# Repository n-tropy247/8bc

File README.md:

# 8bc
8-bit computer on PCB using [Ben Eater's architecture](https://eater.net/8bit)

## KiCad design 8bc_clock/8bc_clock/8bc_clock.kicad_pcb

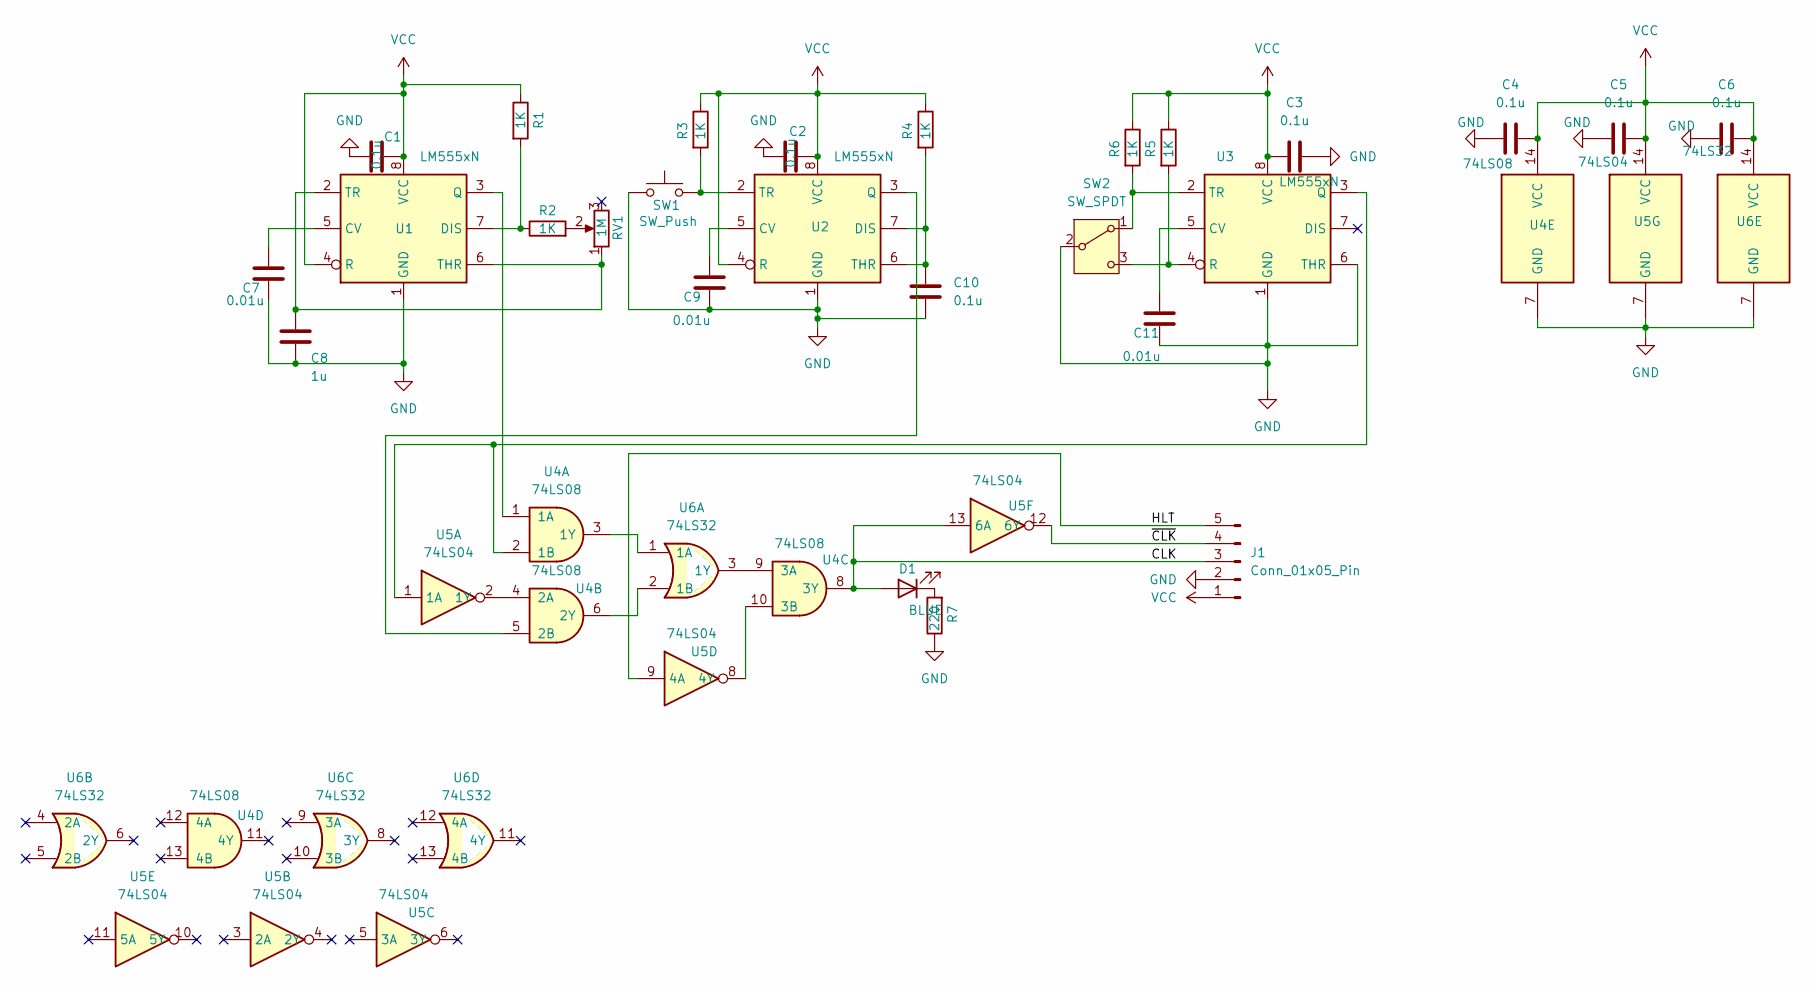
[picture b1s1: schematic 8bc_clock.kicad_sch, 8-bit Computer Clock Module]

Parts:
C1, C2, C3, C4, C5, C6, C10: 0.1u; C_Disc_D3.0mm_W1.6mm_P2.50mm
C7, C9, C11: 0.01u; C_Disc_D3.0mm_W1.6mm_P2.50mm
C8: 1u; C_Disc_D3.0mm_W1.6mm_P2.50mm
D1: BLUE; LED_D3.0mm
J1: Conn_01x05_Pin; PinHeader_1x05_P2.00mm_Vertical
R1, R2, R3, R4, R5, R6: 1K; R_Axial_DIN0204_L3.6mm_D1.6mm_P2.54mm_Vertical
R7: 220; R_Axial_DIN0204_L3.6mm_D1.6mm_P2.54mm_Vertical
RV1: 1M; Potentiometer_Alpha_RD901F-40-00D_Single_Vertical
SW1: SW_Push; SW_PUSH_1P1T_6x3.5mm_H5.0_APEM_MJTP1250
SW2: SW_SPDT; SW_Slide-03_Wuerth-WS-SLTV_10x2.5x6.4_P2.54mm
U1, U2, U3: LM555xN; DIP-8_W7.62mm
U4: 74LS08; DIP-14_W7.62mm_Socket
U5: 74LS04; DIP-14_W7.62mm_Socket
U6: 74LS32; DIP-14_W7.62mm_Socket

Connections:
/CLK: D1.2 (A), J1.3, U4.8 (3Y), U5.13 (6A)
/HLT: J1.5, U5.9 (4A)
/~CLK: J1.4, U5.12 (6Y)
GND: C1.1, C2.1, C3.1, C4.1, C5.1, C6.1, C7.2, C8.2, C9.2, C10.2, C11.2, J1.2, R7.1, SW1.1, SW2.2 (B), U1.1 (GND), U2.1 (GND), U3.1 (GND), U3.6 (THR), U4.7 (GND), U5.7 (GND), U6.7 (GND)
unnamed: D1.1 (K), R7.2
unnamed: R2.2, RV1.2
unnamed: R6.2, SW2.1 (A), U3.2 (TR)
unnamed: R5.2, SW2.3 (C), U3.4 (R)
unnamed: C7.1, U1.5 (CV)
unnamed: R1.2, R2.1, U1.7 (DIS)
unnamed: U1.3 (Q), U4.1 (1A)
unnamed: C8.1, RV1.1, U1.2 (TR), U1.6 (THR)
unnamed: C9.1, U2.5 (CV)
unnamed: C10.1, R4.2, U2.6 (THR), U2.7 (DIS)
unnamed: U2.3 (Q), U4.5 (2B)
unnamed: R3.2, SW1.2, U2.2 (TR)
unnamed: C11.1, U3.5 (CV)
unnamed: U3.3 (Q), U4.2 (1B), U5.1 (1A)
unnamed: U4.3 (1Y), U6.1 (1A)
unnamed: U4.4 (2A), U5.2 (1Y)
unnamed: U4.6 (2Y), U6.2 (1B)
unnamed: U4.9 (3A), U6.3 (1Y)
unnamed: U4.10 (3B), U5.8 (4Y)
VCC: C1.2, C2.2, C3.2, C4.2, C5.2, C6.2, J1.1, R1.1, R3.1, R4.1, R5.1, R6.1, U1.4 (R), U1.8 (VCC), U2.4 (R), U2.8 (VCC), U3.8 (VCC), U4.14 (VCC), U5.14 (VCC), U6.14 (VCC)

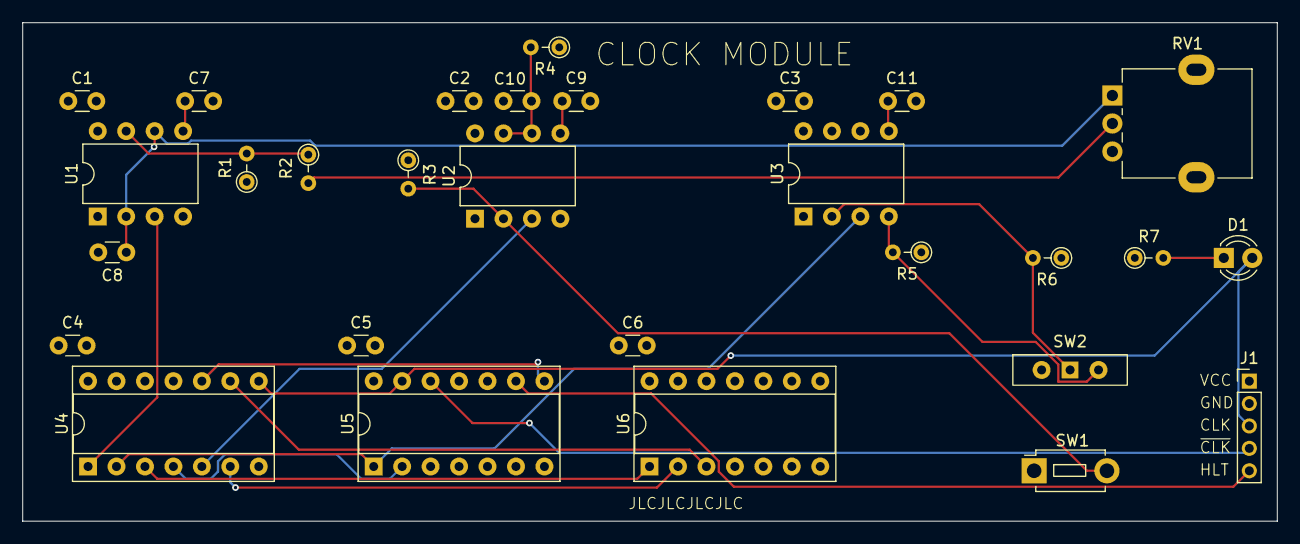
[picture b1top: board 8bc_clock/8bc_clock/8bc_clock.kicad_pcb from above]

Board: 4 copper layers, 112.0 x 44.5 mm, 29 parts (0 on the bottom side), 24 nets.

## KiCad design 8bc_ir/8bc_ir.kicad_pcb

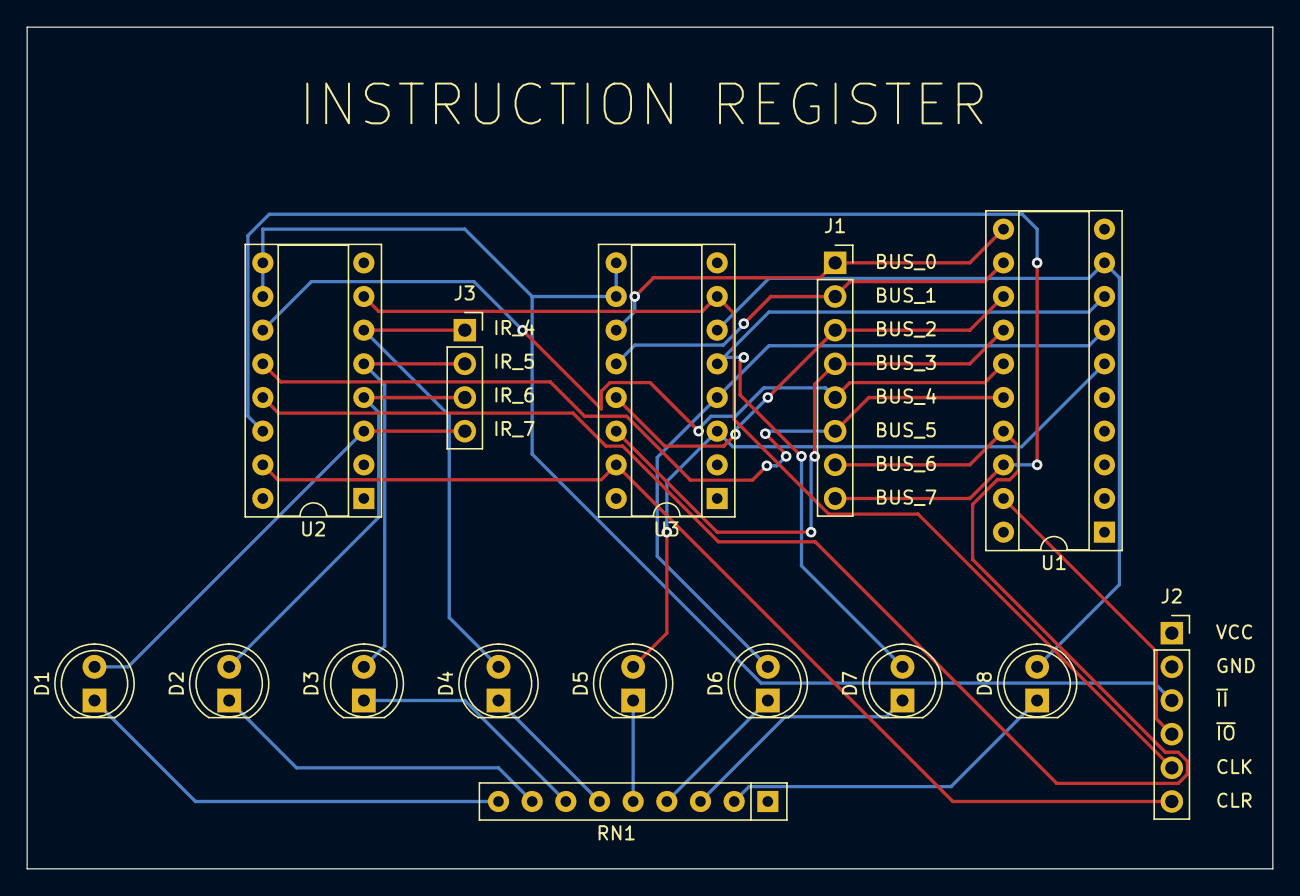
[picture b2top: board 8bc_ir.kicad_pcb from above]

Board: 4 copper layers, 94.0 x 63.5 mm, 15 parts (0 on the bottom side), 30 nets.

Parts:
D1, D2, D3, D4: BLUE; LED_D5.0mm
D5, D6, D7, D8: YELLOW; LED_D5.0mm
J1: Conn_01x08_Pin; PinSocket_1x08_P2.54mm_Vertical
J2: Conn_01x06_Pin; PinSocket_1x06_P2.54mm_Vertical
J3: Conn_01x04_Pin; PinSocket_1x04_P2.54mm_Vertical
RN1: 220; R_Array_SIP9
U1: 74LS245; DIP-20_W7.62mm_Socket
U2, U3: 74LS173; DIP-16_W7.62mm_Socket

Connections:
/BUS_0: J1.1, U1.11 (B7), U3.11 (D3)
/BUS_1: J1.2, U1.12 (B6), U3.12 (D2)
/BUS_2: J1.3, U1.13 (B5), U3.13 (D1)
/BUS_3: J1.4, U1.14 (B4), U3.14 (D0)
/BUS_4: J1.5, U1.15 (B3), U2.11 (D3)
/BUS_5: J1.6, U1.16 (B2), U2.12 (D2)
/BUS_6: J1.7, U1.17 (B1), U2.13 (D1)
/BUS_7: J1.8, U1.18 (B0), U2.14 (D0)
/CLK: J2.5, U2.7 (Cp), U3.7 (Cp)
/CLR: J2.6, U2.15 (Mr), U3.15 (Mr)
/GND: J2.2, RN1.1 (common), U1.10 (GND), U2.1 (Oe1), U2.2 (Oe2), U2.8 (GND), U3.1 (Oe1), U3.2 (Oe2), U3.8 (GND)
/IR_4: D4.2 (A), J3.1, U2.6 (Q3)
/IR_5: D3.2 (A), J3.2, U2.5 (Q2)
/IR_6: D2.2 (A), J3.3, U2.4 (Q1)
/IR_7: D1.2 (A), J3.4, U2.3 (Q0)
/VCC: J2.1, U1.1 (A->B), U1.20 (VCC), U2.16 (VCC), U3.16 (VCC)
/~II: J2.3, U2.9 (E1), U2.10 (E2), U3.9 (E1), U3.10 (E2)
/~IO: J2.4, U1.19 (CE)
unnamed: D1.1 (K), RN1.9 (R8)
unnamed: D2.1 (K), RN1.8 (R7)
unnamed: D3.1 (K), RN1.7 (R6)
unnamed: D4.1 (K), RN1.6 (R5)
unnamed: D5.2 (A), U1.6 (A4), U3.3 (Q0)
unnamed: D5.1 (K), RN1.5 (R4)
unnamed: D6.2 (A), U1.7 (A5), U3.4 (Q1)
unnamed: D6.1 (K), RN1.4 (R3)
unnamed: D7.2 (A), U1.8 (A6), U3.5 (Q2)
unnamed: D7.1 (K), RN1.3 (R2)
unnamed: D8.2 (A), U1.9 (A7), U3.6 (Q3)
unnamed: D8.1 (K), RN1.2 (R1)

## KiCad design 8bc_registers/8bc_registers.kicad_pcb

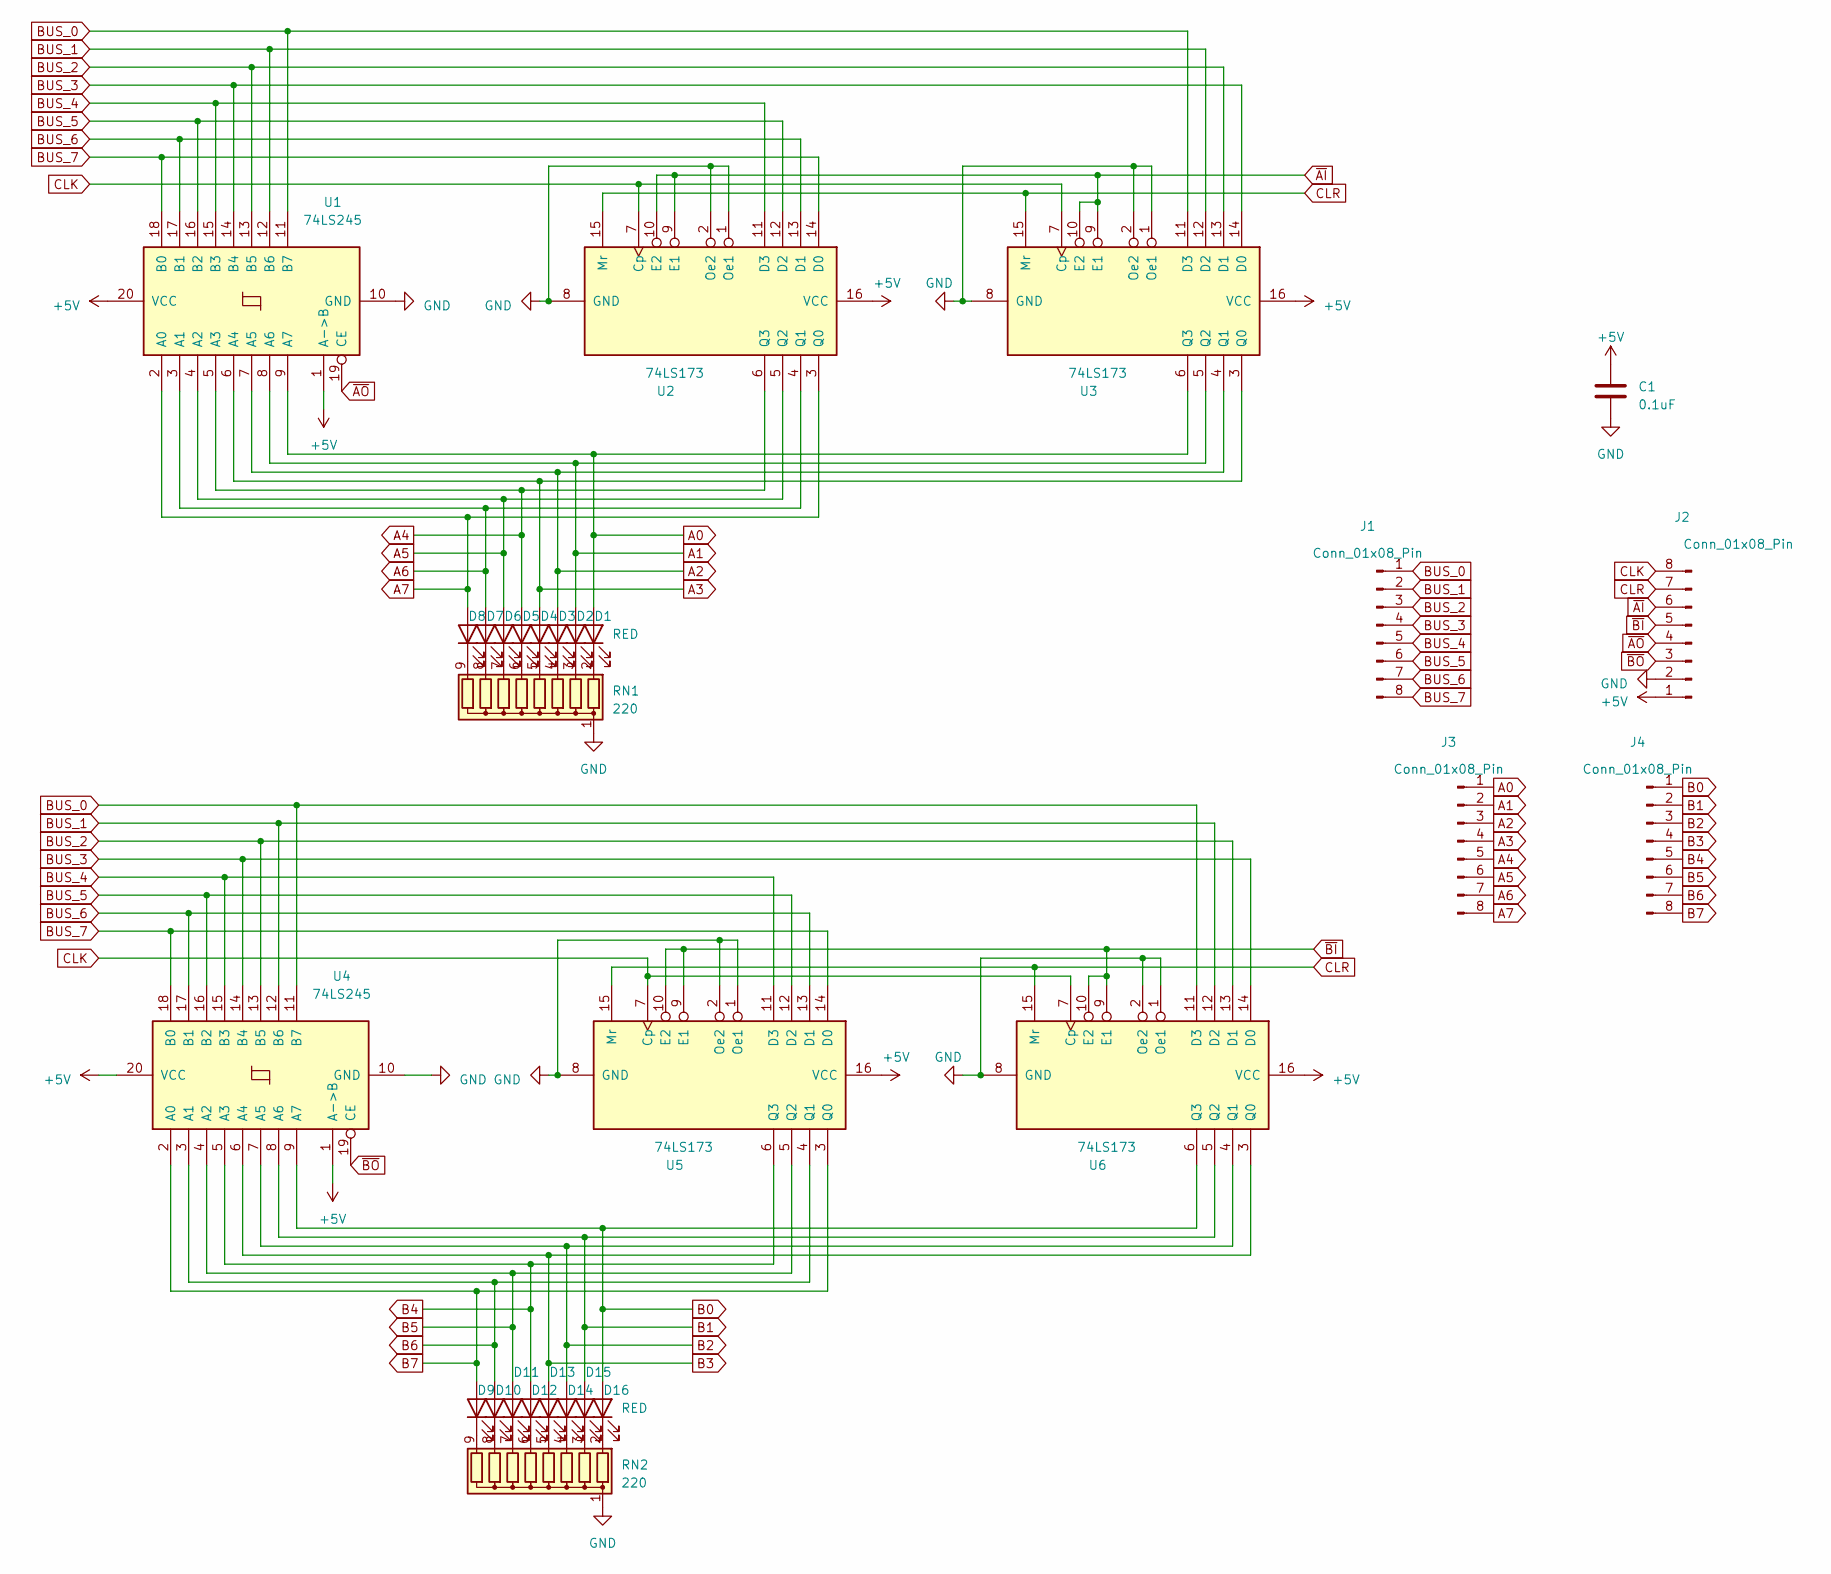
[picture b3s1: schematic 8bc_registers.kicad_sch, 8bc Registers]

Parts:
C1: 0.1uF; CP_Radial_Tantal_D5.0mm_P2.50mm
D1, D2, D3, D4, D5, D6, D7, D8, D9, D10, D11, D12, D13, D14, D15, D16: RED; LED_D8.0mm
J1, J2, J3, J4: Conn_01x08_Pin; PinSocket_1x08_P2.54mm_Vertical
RN1, RN2: 220; R_Array_SIP9
U1, U4: 74LS245; DIP-20_W7.62mm_Socket
U2, U3, U5, U6: 74LS173; DIP-16_W7.62mm_Socket

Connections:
+5V: C1.1, J2.1, U1.1 (A->B), U1.20 (VCC), U2.16 (VCC), U3.16 (VCC), U4.1 (A->B), U4.20 (VCC), U5.16 (VCC), U6.16 (VCC)
A0: D1.2 (A), J3.1, U1.9 (A7), U3.6 (Q3)
A1: D2.2 (A), J3.2, U1.8 (A6), U3.5 (Q2)
A2: D3.2 (A), J3.3, U1.7 (A5), U3.4 (Q1)
A3: D4.2 (A), J3.4, U1.6 (A4), U3.3 (Q0)
A4: D5.2 (A), J3.5, U1.5 (A3), U2.6 (Q3)
A5: D6.2 (A), J3.6, U1.4 (A2), U2.5 (Q2)
A6: D7.2 (A), J3.7, U1.3 (A1), U2.4 (Q1)
A7: D8.2 (A), J3.8, U1.2 (A0), U2.3 (Q0)
B0: D16.2 (A), J4.1, U4.9 (A7), U6.6 (Q3)
B1: D15.2 (A), J4.2, U4.8 (A6), U6.5 (Q2)
B2: D14.2 (A), J4.3, U4.7 (A5), U6.4 (Q1)
B3: D13.2 (A), J4.4, U4.6 (A4), U6.3 (Q0)
B4: D12.2 (A), J4.5, U4.5 (A3), U5.6 (Q3)
B5: D11.2 (A), J4.6, U4.4 (A2), U5.5 (Q2)
B6: D10.2 (A), J4.7, U4.3 (A1), U5.4 (Q1)
B7: D9.2 (A), J4.8, U4.2 (A0), U5.3 (Q0)
BUS_0: J1.1, U1.11 (B7), U3.11 (D3), U4.11 (B7), U6.11 (D3)
BUS_1: J1.2, U1.12 (B6), U3.12 (D2), U4.12 (B6), U6.12 (D2)
BUS_2: J1.3, U1.13 (B5), U3.13 (D1), U4.13 (B5), U6.13 (D1)
BUS_3: J1.4, U1.14 (B4), U3.14 (D0), U4.14 (B4), U6.14 (D0)
BUS_4: J1.5, U1.15 (B3), U2.11 (D3), U4.15 (B3), U5.11 (D3)
BUS_5: J1.6, U1.16 (B2), U2.12 (D2), U4.16 (B2), U5.12 (D2)
BUS_6: J1.7, U1.17 (B1), U2.13 (D1), U4.17 (B1), U5.13 (D1)
BUS_7: J1.8, U1.18 (B0), U2.14 (D0), U4.18 (B0), U5.14 (D0)
CLK: J2.8, U2.7 (Cp), U3.7 (Cp), U5.7 (Cp), U6.7 (Cp)
CLR: J2.7, U2.15 (Mr), U3.15 (Mr), U5.15 (Mr), U6.15 (Mr)
GND: C1.2, J2.2, RN1.1 (common), RN2.1 (common), U1.10 (GND), U2.1 (Oe1), U2.2 (Oe2), U2.8 (GND), U3.1 (Oe1), U3.2 (Oe2), U3.8 (GND), U4.10 (GND), U5.1 (Oe1), U5.2 (Oe2), U5.8 (GND), U6.1 (Oe1), U6.2 (Oe2), U6.8 (GND)
unnamed: D1.1 (K), RN1.2 (R1)
unnamed: D2.1 (K), RN1.3 (R2)
unnamed: D3.1 (K), RN1.4 (R3)
unnamed: D4.1 (K), RN1.5 (R4)
unnamed: D5.1 (K), RN1.6 (R5)
unnamed: D6.1 (K), RN1.7 (R6)
unnamed: D7.1 (K), RN1.8 (R7)
unnamed: D8.1 (K), RN1.9 (R8)
unnamed: D9.1 (K), RN2.9 (R8)
unnamed: D10.1 (K), RN2.8 (R7)
unnamed: D11.1 (K), RN2.7 (R6)
unnamed: D12.1 (K), RN2.6 (R5)
unnamed: D13.1 (K), RN2.5 (R4)
unnamed: D14.1 (K), RN2.4 (R3)
unnamed: D15.1 (K), RN2.3 (R2)
unnamed: D16.1 (K), RN2.2 (R1)
~AI: J2.6, U2.9 (E1), U2.10 (E2), U3.9 (E1), U3.10 (E2)
~AO: J2.4, U1.19 (CE)
~BI: J2.5, U5.9 (E1), U5.10 (E2), U6.9 (E1), U6.10 (E2)
~BO: J2.3, U4.19 (CE)

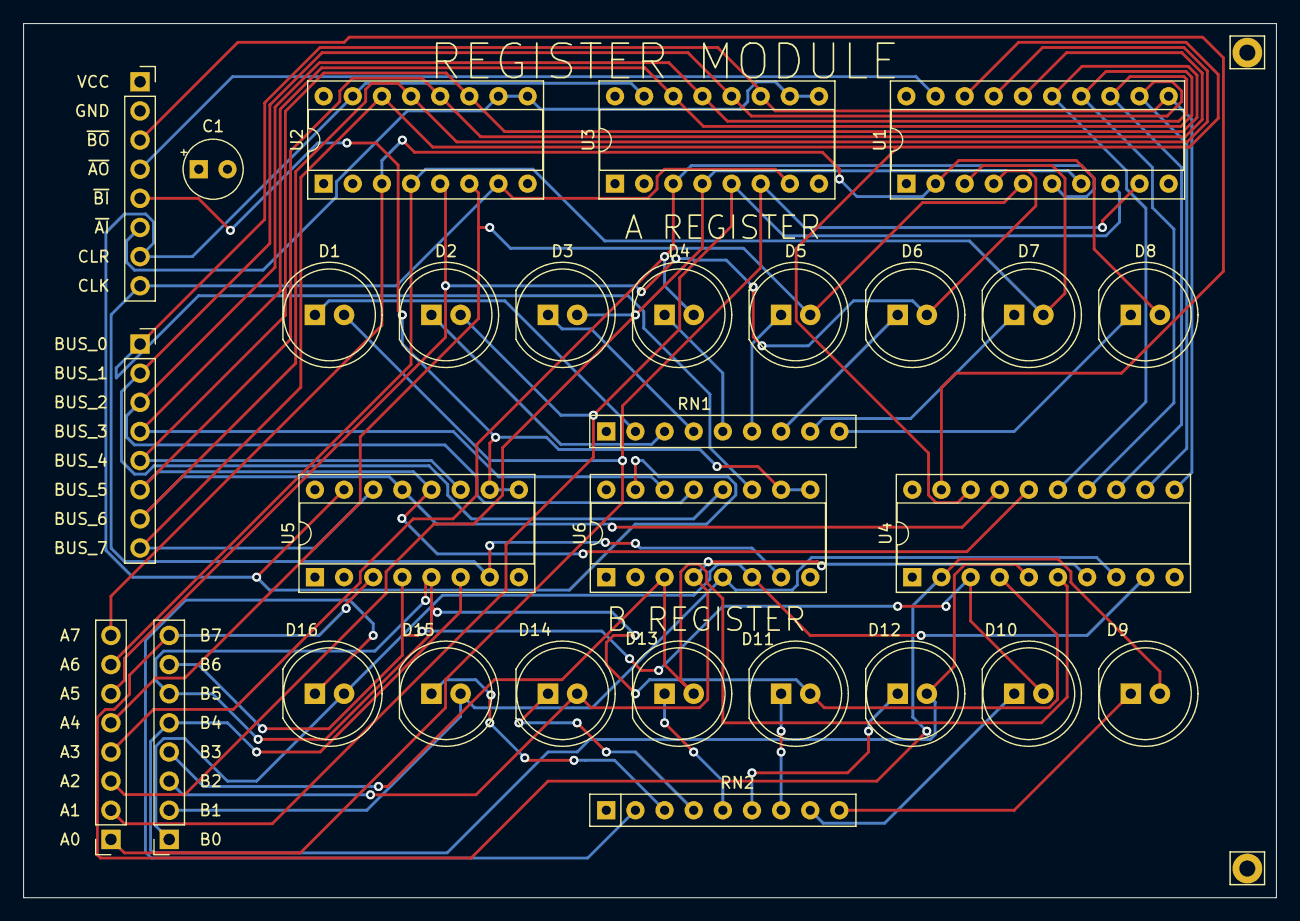
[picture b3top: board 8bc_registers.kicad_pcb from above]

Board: 4 copper layers, 109.2 x 76.2 mm, 29 parts (0 on the bottom side), 48 nets.

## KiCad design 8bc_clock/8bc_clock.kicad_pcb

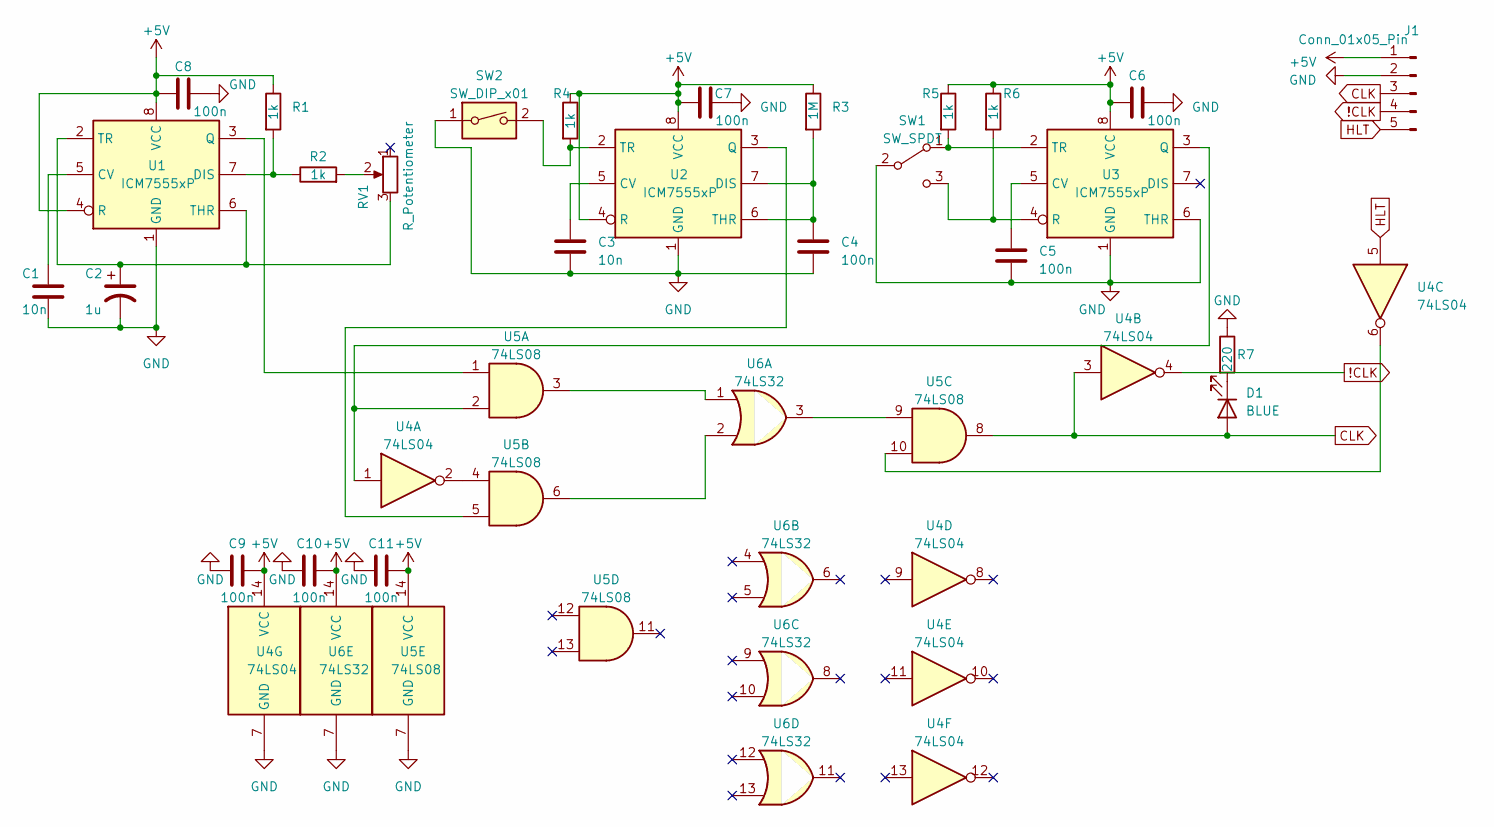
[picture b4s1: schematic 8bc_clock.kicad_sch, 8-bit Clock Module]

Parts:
C1: 10n; C_Disc_D4.7mm_W2.5mm_P5.00mm
C2: 1u; CP_Radial_D8.0mm_P5.00mm
C3: 10n; C_Radial_D8.0mm_H7.0mm_P3.50mm
C4, C5, C6, C7, C8, C9, C10, C11: 100n; C_Radial_D8.0mm_H7.0mm_P3.50mm
D1: BLUE; LED_D8.0mm
J1: Conn_01x05_Pin; PinSocket_1x05_P2.54mm_Vertical
R1, R2, R4, R5, R6: 1k; R_Axial_DIN0207_L6.3mm_D2.5mm_P7.62mm_Horizontal
R3: 1M; R_Axial_DIN0207_L6.3mm_D2.5mm_P7.62mm_Horizontal
R7: 220; R_Axial_DIN0207_L6.3mm_D2.5mm_P7.62mm_Horizontal
RV1: R_Potentiometer; Potentiometer_Bourns_PTV09A-1_Single_Vertical
SW1: SW_SPDT; SW_Slide_1P2T_CK_OS102011MS2Q
SW2: SW_DIP_x01; SW_PUSH_6mm_H7.3mm
U1, U2, U3: ICM7555xP; DIP-8_W7.62mm
U4: 74LS04; DIP-14_W7.62mm
U5: 74LS08; DIP-14_W7.62mm
U6: 74LS32; DIP-14_W7.62mm

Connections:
!CLK: J1.4, U4.4
+5V: C6.1, C7.1, C8.1, C9.2, C10.2, C11.2, J1.1, R1.1, R3.1, R4.1, R5.1, R6.1, U1.4 (R), U1.8 (VCC), U2.4 (R), U2.8 (VCC), U3.8 (VCC), U4.14 (VCC), U5.14 (VCC), U6.14 (VCC)
CLK: D1.2 (A), J1.3, U4.3, U5.8
GND: C1.2, C2.2, C3.2, C4.2, C5.2, C6.2, C7.2, C8.2, C9.1, C10.1, C11.1, J1.2, R7.1, SW1.2 (B), SW2.1, U1.1 (GND), U2.1 (GND), U3.1 (GND), U3.6 (THR), U4.7 (GND), U5.7 (GND), U6.7 (GND)
HLT: J1.5, U4.5
unnamed: D1.1 (K), R7.2
unnamed: R2.2, RV1.2
unnamed: R5.2, SW1.1 (A), U3.2 (TR)
unnamed: R6.2, SW1.3 (C), U3.4 (R)
unnamed: C1.1, U1.5 (CV)
unnamed: R1.2, R2.1, U1.7 (DIS)
unnamed: U1.3 (Q), U5.1
unnamed: C2.1, RV1.3, U1.2 (TR), U1.6 (THR)
unnamed: C3.1, U2.5 (CV)
unnamed: C4.1, R3.2, U2.6 (THR), U2.7 (DIS)
unnamed: U2.3 (Q), U5.5
unnamed: R4.2, SW2.2, U2.2 (TR)
unnamed: C5.1, U3.5 (CV)
unnamed: U3.3 (Q), U4.1, U5.2
unnamed: U4.2, U5.4
unnamed: U4.6, U5.10
unnamed: U5.3, U6.1
unnamed: U5.6, U6.2
unnamed: U5.9, U6.3

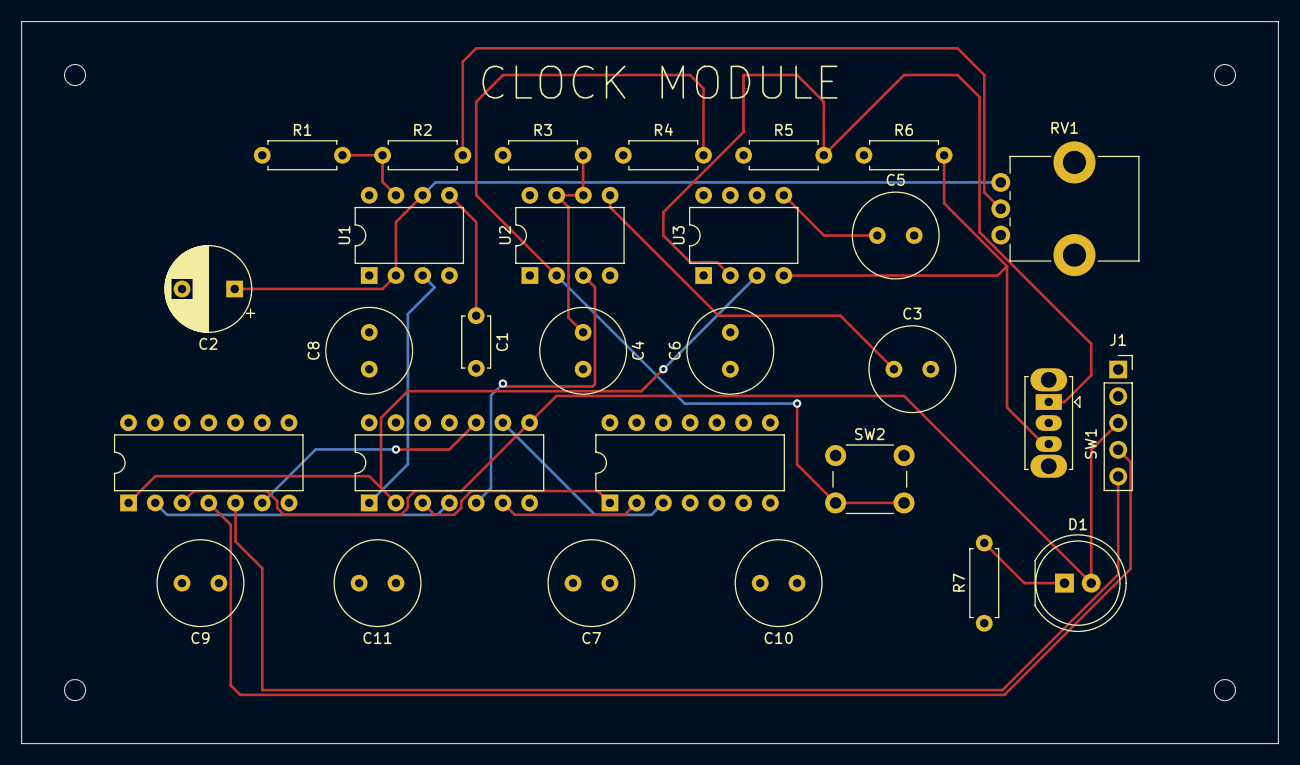
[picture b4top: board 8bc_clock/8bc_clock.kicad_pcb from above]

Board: 4 copper layers, 119.4 x 68.6 mm, 29 parts (0 on the bottom side), 24 nets.

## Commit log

2023-02-28 init
2023-03-01 added register circuit
2023-03-01 added supersheet
2023-03-06 added instr reg
2023-03-06 updated root
2023-03-16 fixed R value
2023-05-17 fixed clock circuit error
2023-05-19 fixed schematic error
2024-06-08 rebuilt clock module
